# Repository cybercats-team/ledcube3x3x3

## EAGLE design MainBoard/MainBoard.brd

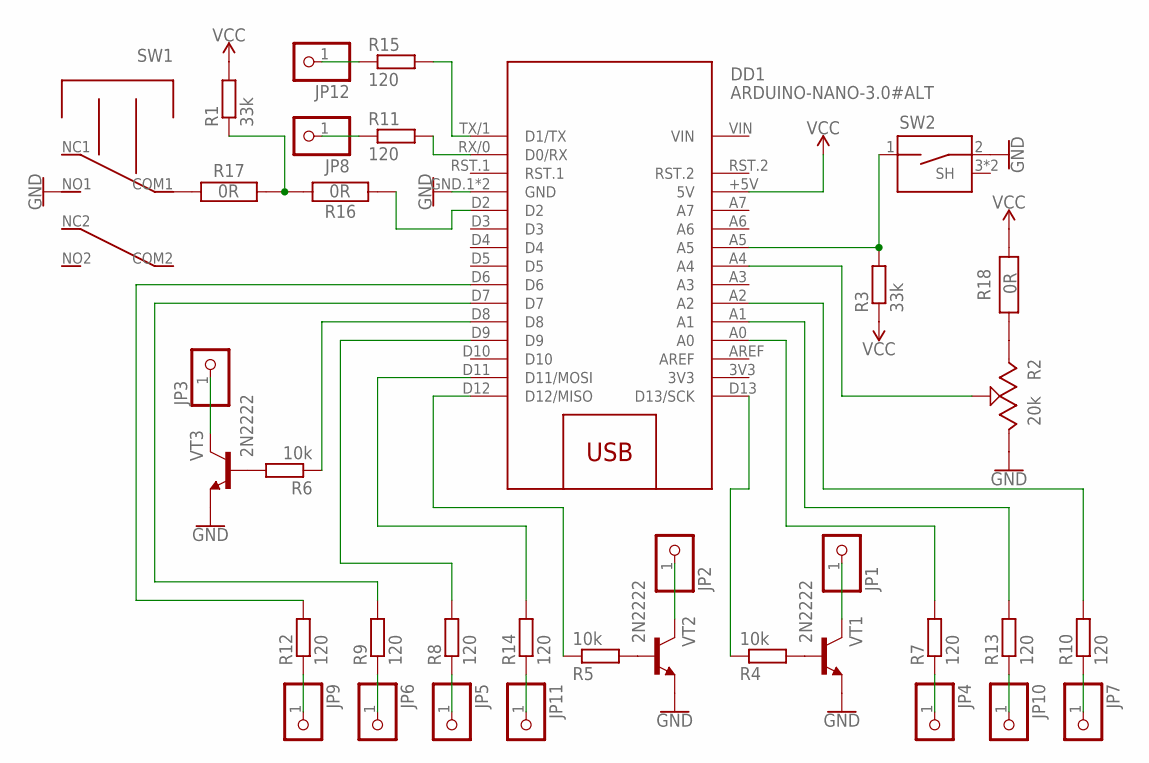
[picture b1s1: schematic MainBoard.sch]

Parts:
DD1: ARDUINO-NANO-3.0#ALT
JP1, JP2, JP3, JP4, JP5, JP6, JP7, JP8, JP9, JP10, JP11, JP12: PINHD-1X1; 1X01
R1, R3: 33k; R0805
R2: 20k; TRIM_RV100F-30-4K1B-B10K-B301
R4, R5, R6: 10k; R0805
R7, R8, R9, R10, R11, R12, R13, R14, R15: 120; R0805
R16, R17: 0R; WRIS-KSKE_2512_6.3X3.2X0.6(LXWXH)
R18: 0R; WRIS-KSKE_1206_3.1X1.6X0.6X0.3(LXWXHXPW)
SW1: PS22-F03; PS-22F03
SW2: 1571610-2
VT1, VT2, VT3: 2N2222; SOT23-3

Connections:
3V3: DD1.3V3
GND: DD1.GND.1 (GND), DD1.GND.2 (GND), R2.3, SW1.NO1, SW2.2, VT1.2 (E), VT2.2 (E), VT3.2 (E)
unnamed: R1.1, R16.1, R17.2
unnamed: DD1.A5, R3.2, SW2.1
unnamed: DD1.A4, R2.2
unnamed: JP1.1, VT1.3 (C)
unnamed: R4.2, VT1.1 (B)
unnamed: R5.2, VT2.1 (B)
unnamed: R6.2, VT3.1 (B)
unnamed: JP2.1, VT2.3 (C)
unnamed: JP3.1, VT3.3 (C)
unnamed: JP8.1, R11.1
unnamed: DD1.D13 (D13/SCK), R4.1
unnamed: DD1.D8, R6.1
unnamed: JP4.1, R7.1
unnamed: JP5.1, R8.1
unnamed: JP6.1, R9.1
unnamed: JP7.1, R10.1
unnamed: DD1.RX/0 (D0/RX), R11.2
unnamed: JP9.1, R12.1
unnamed: JP10.1, R13.1
unnamed: JP11.1, R14.1
unnamed: JP12.1, R15.1
unnamed: DD1.A0, R7.2
unnamed: DD1.D12 (D12/MISO), R5.1
unnamed: DD1.D7, R9.2
unnamed: DD1.A1, R13.2
unnamed: DD1.D6, R12.2
unnamed: DD1.D9, R8.2
unnamed: DD1.A2, R10.2
unnamed: DD1.D11 (D11/MOSI), R14.2
unnamed: DD1.TX/1 (D1/TX), R15.2
unnamed: DD1.D2, R16.2
unnamed: R17.1, SW1.COM1
unnamed: R2.1, R18.1
VCC: DD1.+5V (5V), R1.2, R3.1, R18.2
VIN: DD1.VIN

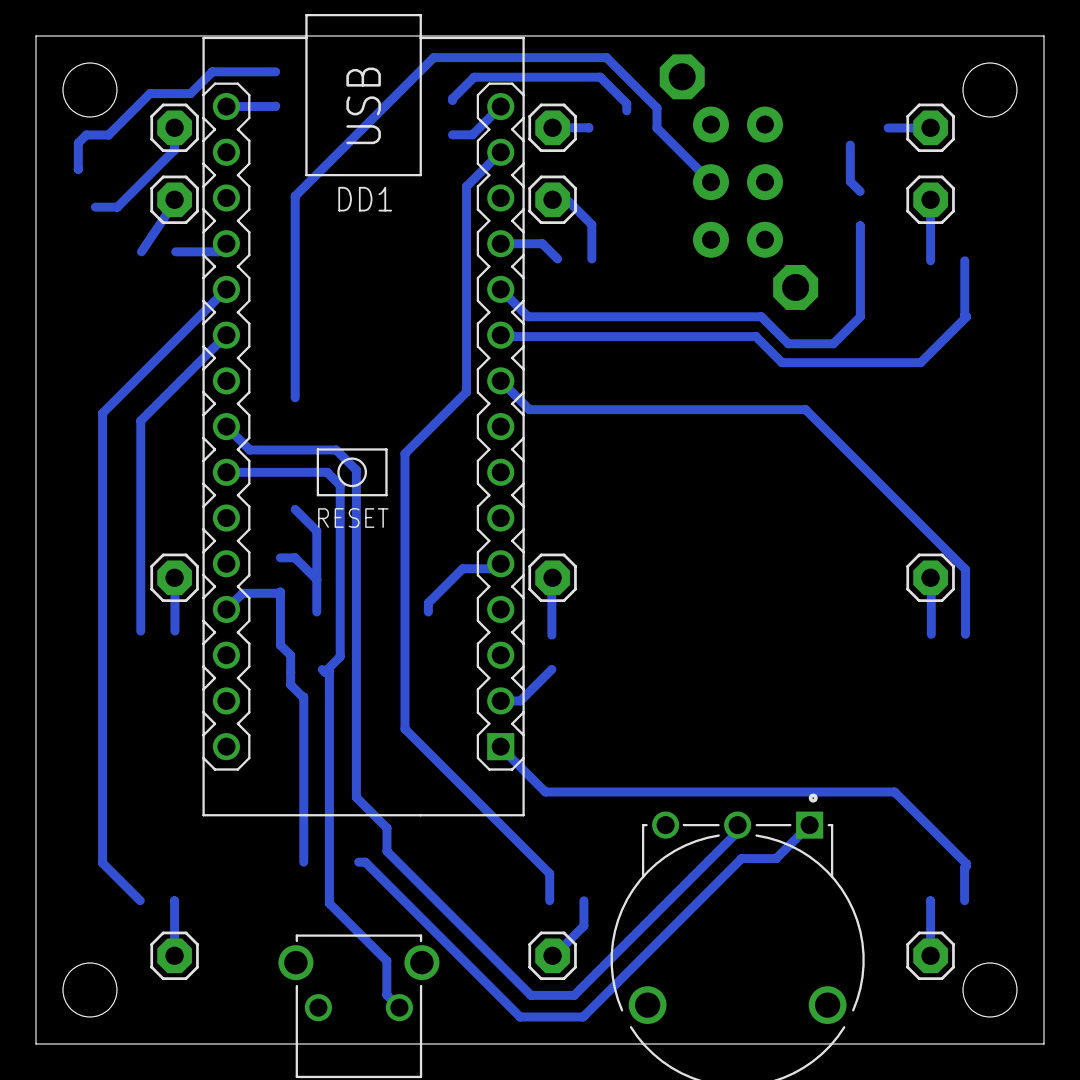
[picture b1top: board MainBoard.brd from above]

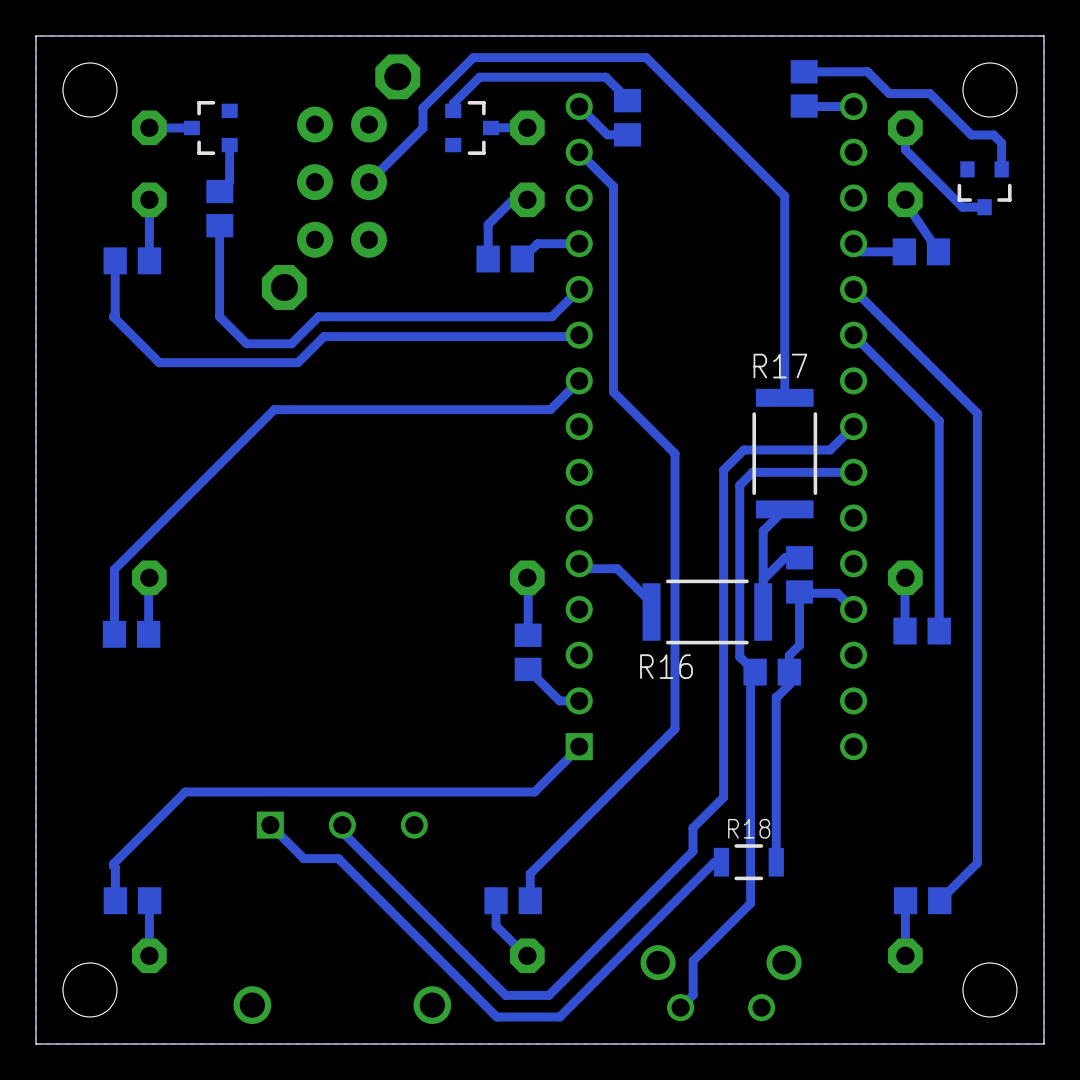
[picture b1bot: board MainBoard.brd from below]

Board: 2 copper layers, 56.0 x 56.0 mm, 36 parts (20 on the bottom side), 35 nets.

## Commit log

2020-10-18 remove gerber
2021-01-05 add controls
2021-01-05 implement IControlsDelegate
2021-01-05 adjust ratio range
2021-01-07 refactor device mode, fix warnings
2021-01-07 move each animation to a separate device mode, select random mode at startup
2021-01-07 select next random animation after each animation done
2021-01-07 switch mode using button
2021-01-07 fix debouncer
2021-01-16 remove .vscode
2021-01-16 add gitignore
2021-01-16 update gitignore
2021-01-17 add power switch
2021-01-17 power switch implementation
2021-01-17 fix build errors
2021-01-17 fix power btn
2021-01-18 refactor power switch
2021-01-18 finish refactoring power switch
2021-01-18 fix power off

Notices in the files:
parts and their libraries:
SparkFun-DiscreteSemi: Licensing: Creative Commons ShareAlike 4.0 International - https://creativecommons.org/licenses/by-sa/4.0
diy-modules: Released under the Creative Commons Attribution 4.0 International License: http://creativecommons.org/licenses/by/4.0
